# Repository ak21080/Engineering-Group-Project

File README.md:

# Engineering-Group-Project
Group Project data
source for Arduino shield http://eagle.autodesk.com/eagle/libraries?button=&q%5Bs%5D=uploaded_at+asc&q%5Btitle_or_author_or_description_cont%5D=arduino (arduino.zip)

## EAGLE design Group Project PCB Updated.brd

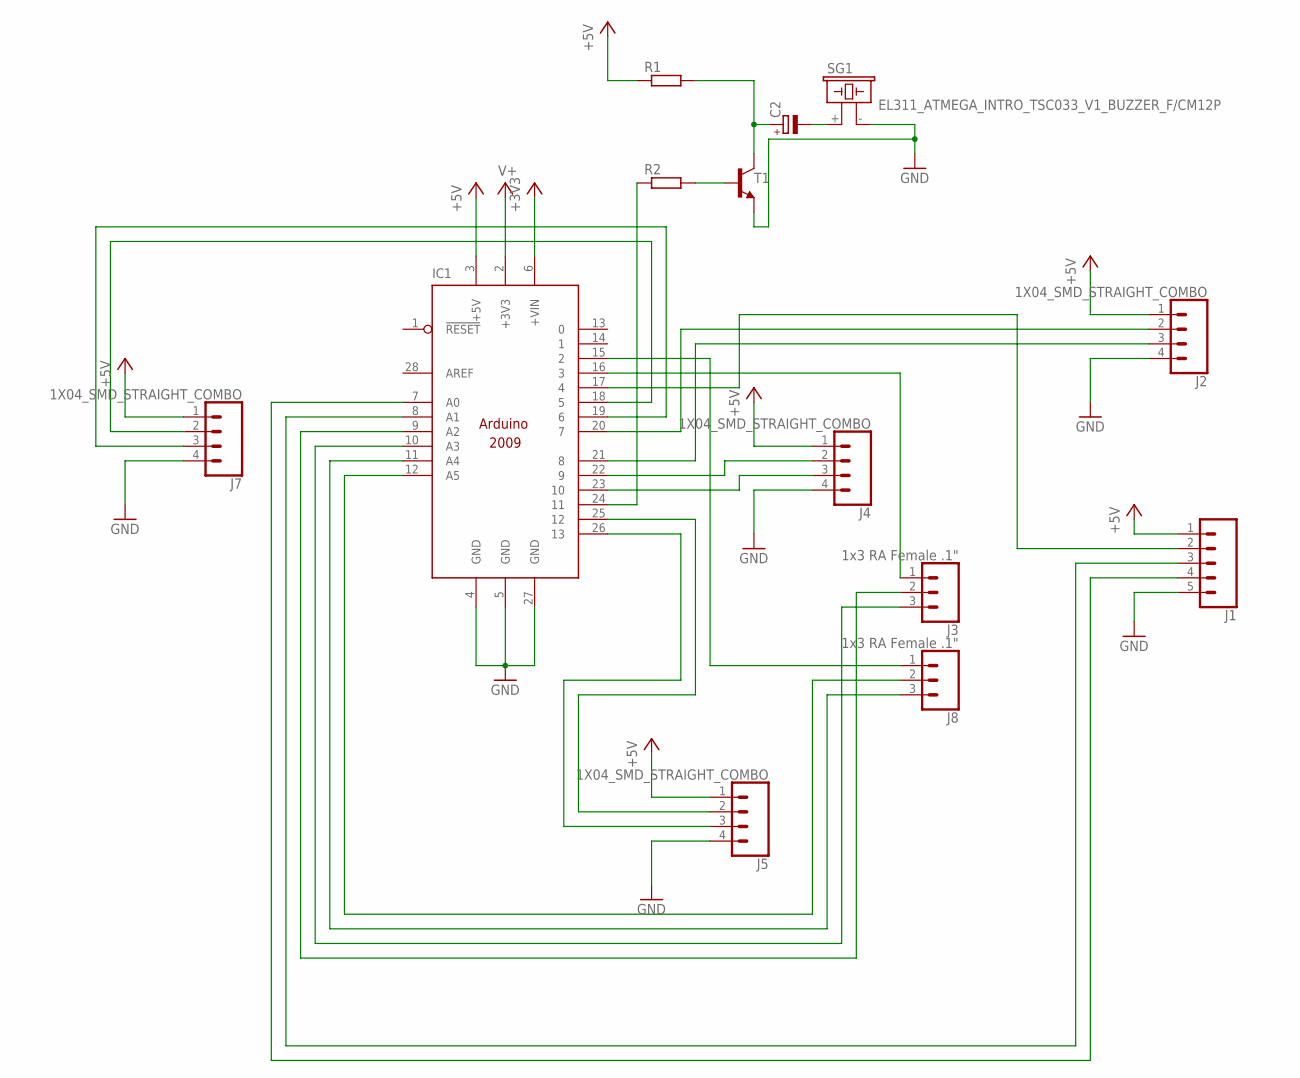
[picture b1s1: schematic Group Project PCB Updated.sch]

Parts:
C2: RCL_CPOL-EUE3.5-8; ELECTROLYTIC_CAP_RCL_E3,5-8
IC1: ARDUINO2009_10; ARDUINO2009
J1: CONN_05PTH_LONGPADS; 1X05_LONGPADS
J2, J4, J5, J7: 1X04_SMD_STRAIGHT_COMBO; 1X04_LONGPADS
J3, J8: 1x3 RA Female .1"; 1X03_LONGPADS
R1, R2: R-EU_0207/10; 0207/10
SG1: EL311_ATMEGA_INTRO_TSC033_V1_BUZZER_F/CM12P
T1: 2N1613-NPN-TO92-EBC; TO92-EBC

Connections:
+3V3: IC1.6 (+VIN)
+5V: IC1.3 (+5V), J1.1, J2.1, J4.1, J5.1, J7.1, R1.1
GND: IC1.4 (GND), IC1.5 (GND), IC1.27 (GND), J1.5, J2.4, J4.4, J5.4, J7.4, SG1.- (2), T1.E
unnamed: R2.2, T1.B
unnamed: C2.-, SG1.+ (1)
unnamed: IC1.23 (10), J4.3
unnamed: IC1.22 (9), J4.2
unnamed: IC1.21 (8), J2.3
unnamed: IC1.20 (7), J2.2
unnamed: IC1.19 (6), J7.3
unnamed: IC1.18 (5), J7.2
unnamed: IC1.25 (12), J5.2
unnamed: IC1.26 (13), J5.3
unnamed: C2.+, R1.2, T1.C
unnamed: IC1.15 (2), J8.1
unnamed: IC1.16 (3), J3.1
unnamed: IC1.24 (11), R2.1
unnamed: IC1.9 (A2), J3.2
unnamed: IC1.11 (A4), J8.3
unnamed: IC1.10 (A3), J3.3
unnamed: IC1.12 (A5), J8.2
unnamed: IC1.7 (A0), J1.4
unnamed: IC1.8 (A1), J1.3
unnamed: IC1.17 (4), J1.2
V+: IC1.2 (+3V3)

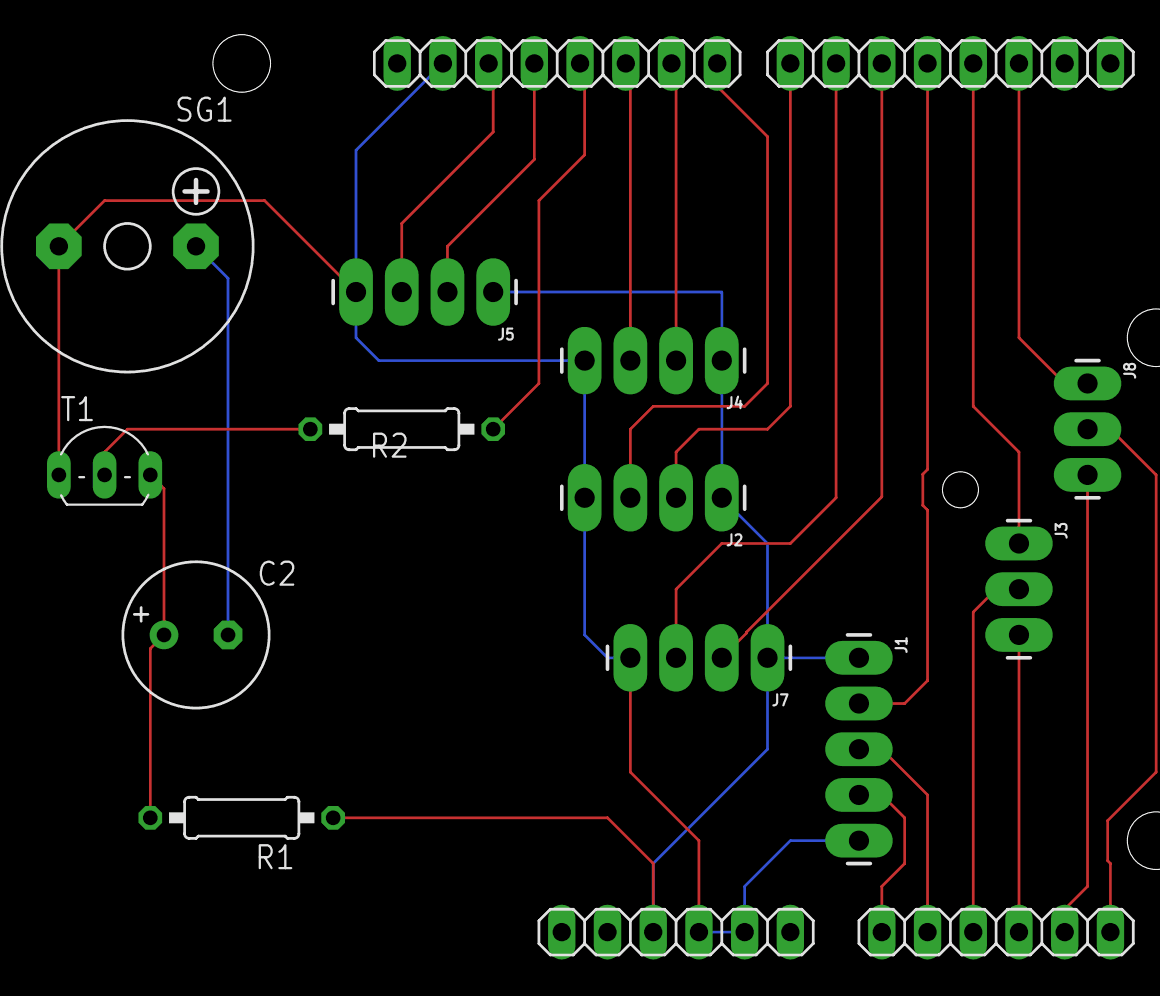
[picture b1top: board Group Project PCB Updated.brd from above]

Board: 2 copper layers, 13 parts (0 on the bottom side), 23 nets.

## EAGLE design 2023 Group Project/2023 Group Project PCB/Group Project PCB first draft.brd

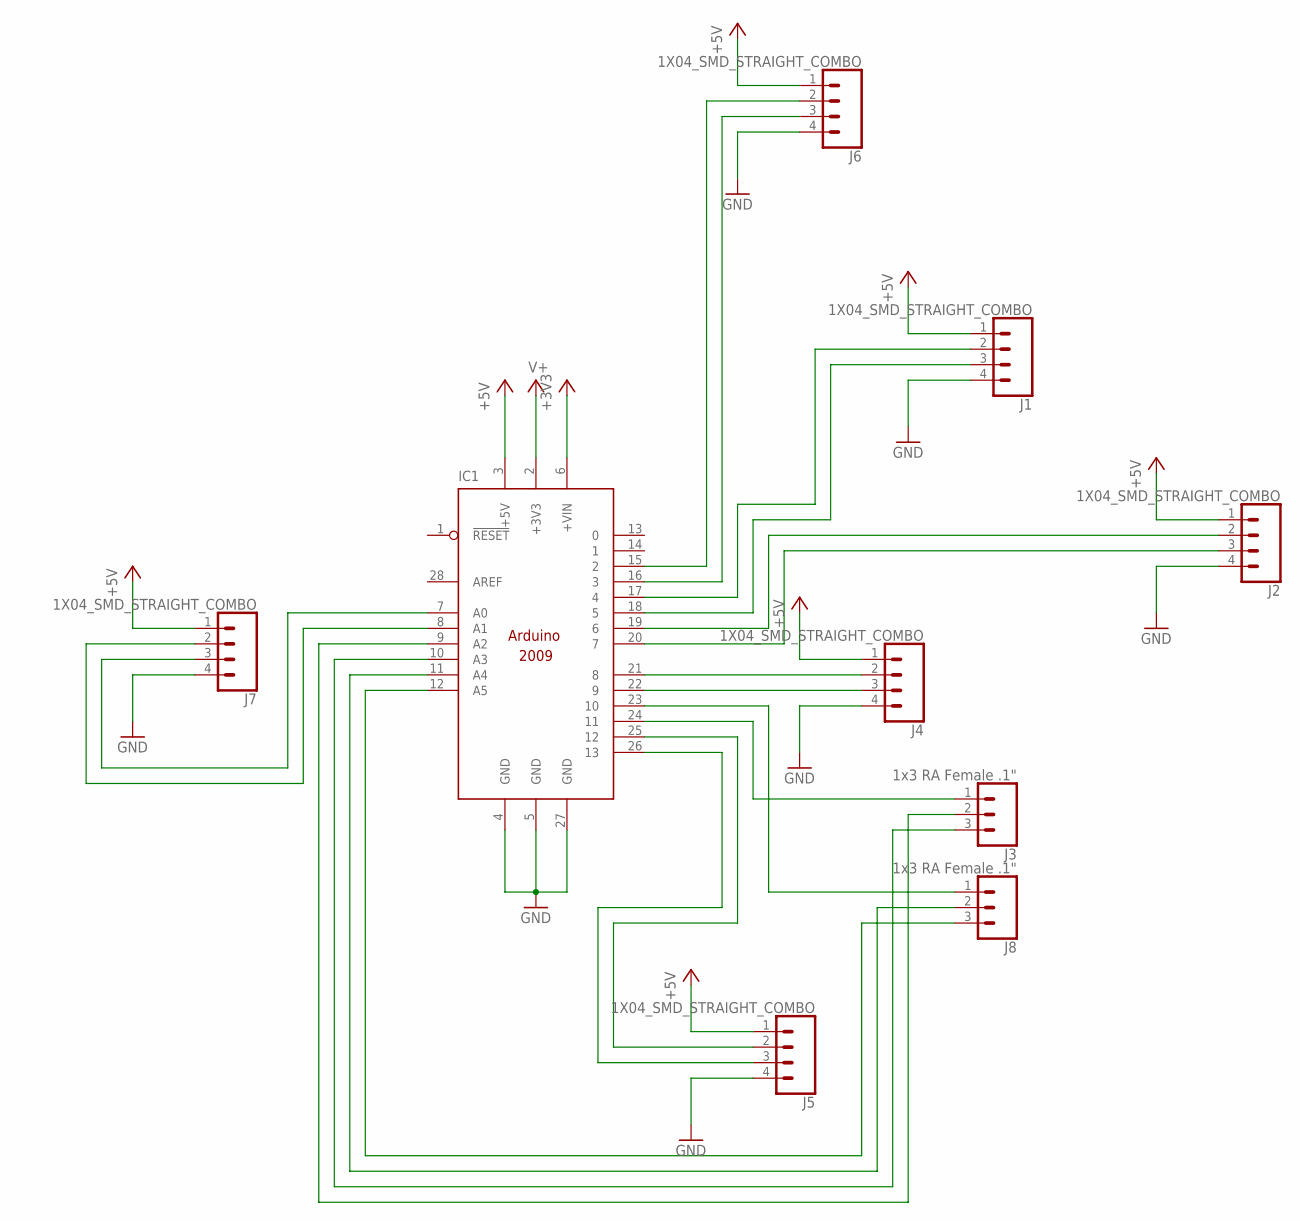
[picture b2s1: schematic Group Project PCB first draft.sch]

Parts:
IC1: ARDUINO2009_10; ARDUINO2009
J1, J2, J4, J5, J6, J7: 1X04_SMD_STRAIGHT_COMBO; 1X04_LONGPADS
J3, J8: 1x3 RA Female .1"; 1X03_LONGPADS

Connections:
+3V3: IC1.6 (+VIN)
+5V: IC1.3 (+5V), J1.1, J2.1, J4.1, J5.1, J6.1, J7.1
GND: IC1.4 (GND), IC1.5 (GND), IC1.27 (GND), J1.4, J2.4, J4.4, J5.4, J6.4, J7.4
unnamed: IC1.17 (4), J1.2
unnamed: IC1.18 (5), J1.3
unnamed: IC1.21 (8), J4.2
unnamed: IC1.22 (9), J4.3
unnamed: IC1.19 (6), J2.2
unnamed: IC1.20 (7), J2.3
unnamed: IC1.8 (A1), J7.2
unnamed: IC1.7 (A0), J7.3
unnamed: IC1.25 (12), J5.2
unnamed: IC1.26 (13), J5.3
unnamed: IC1.15 (2), J6.2
unnamed: IC1.16 (3), J6.3
unnamed: IC1.23 (10), J8.1
unnamed: IC1.24 (11), J3.1
unnamed: IC1.9 (A2), J3.2
unnamed: IC1.11 (A4), J8.2
unnamed: IC1.10 (A3), J3.3
unnamed: IC1.12 (A5), J8.3
V+: IC1.2 (+3V3)

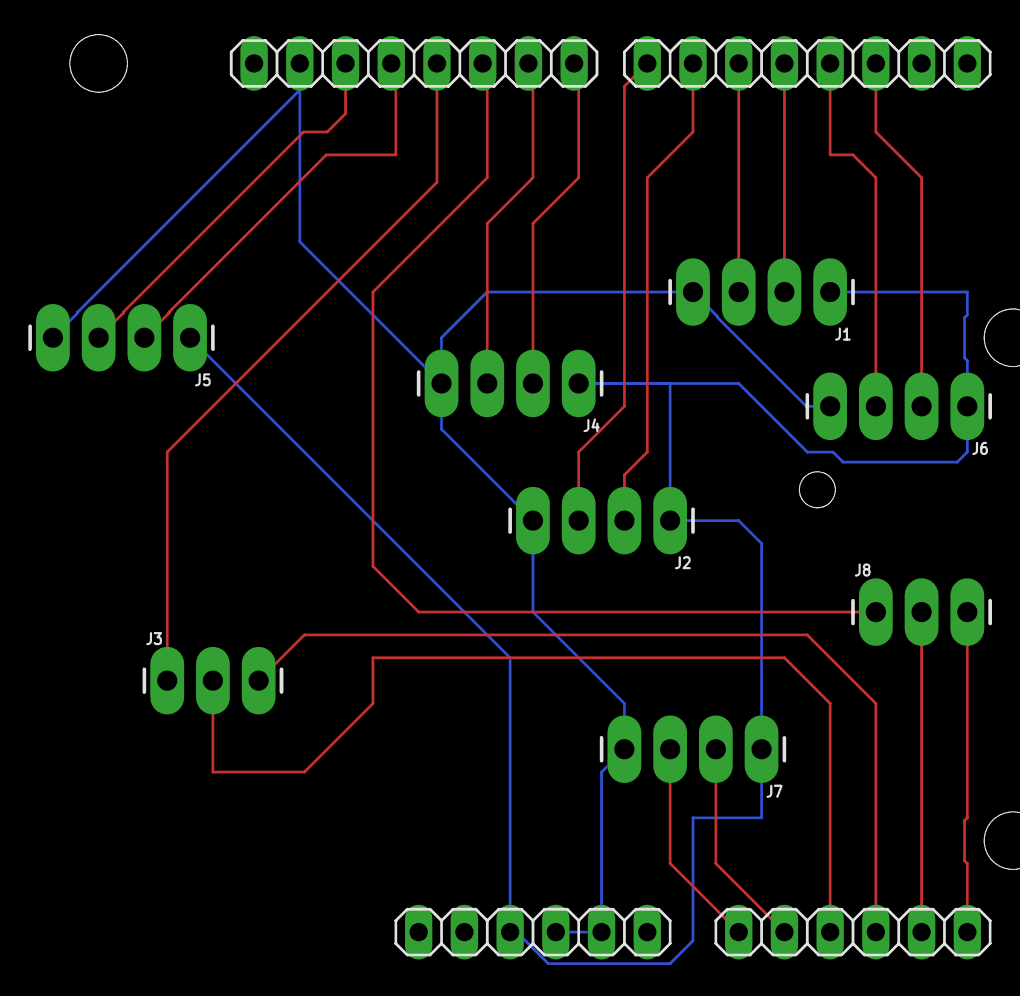
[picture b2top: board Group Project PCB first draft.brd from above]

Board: 2 copper layers, 9 parts (0 on the bottom side), 20 nets.

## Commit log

2023-11-27 Add files via upload
    Updated PCB schematic with the removal of two ultra-sonic sensors and an addition of a buzzer
2023-11-27 Add files via upload
    Updated PCB with removal of 2 four pin connectors and an added buzzer
